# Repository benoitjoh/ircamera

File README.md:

# ircamera

## to install on raspberrypi as user pi

login as user pi

git clone git@github.com:benoitjoh/ircamera.git

cd ircamera

sudo ./install.sh

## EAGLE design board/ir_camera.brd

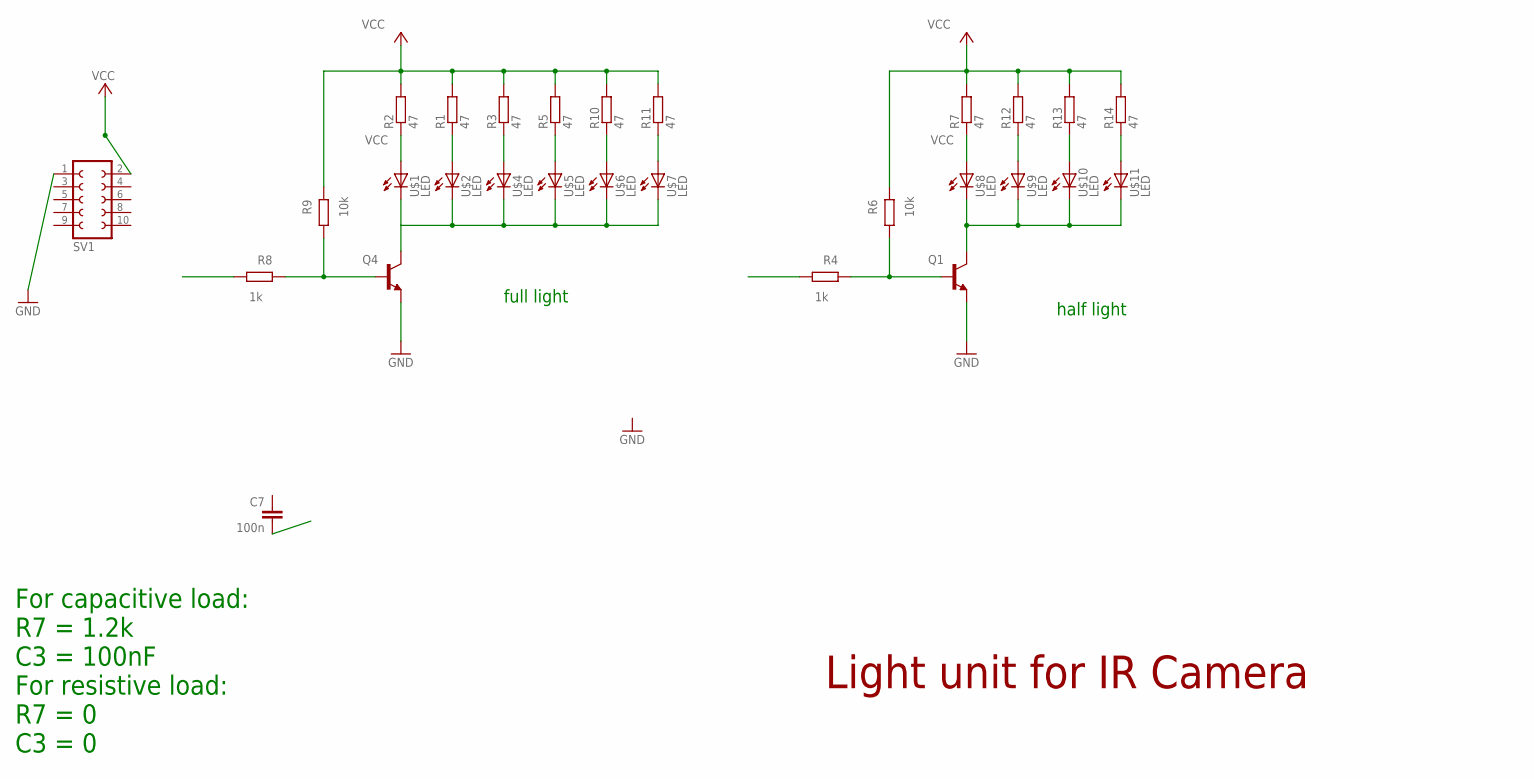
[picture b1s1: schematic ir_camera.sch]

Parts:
C7: 100n; C050-024X044
Q1, Q4: BC548; TO92-EBC
R1, R2, R3, R5, R7, R10, R11, R12, R13, R14: 47; R_0207/2V
R4, R8: 1k; R_0207/2V
R6, R9: 10k; R_0207/2V
SV1: FE05-2
U$1, U$2, U$4, U$5, U$6, U$7, U$8, U$9, U$10, U$11: LED; LED_LD260

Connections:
GND: Q1.E, Q4.E, SV1.1
unnamed: Q4.B, R8.1, R9.1
unnamed: R2.1, U$1.A
unnamed: R1.1, U$2.A
unnamed: R3.1, U$4.A
unnamed: R5.1, U$5.A
unnamed: R10.1, U$6.A
unnamed: R11.1, U$7.A
unnamed: Q4.C, U$1.K (C), U$2.K (C), U$4.K (C), U$5.K (C), U$6.K (C), U$7.K (C)
unnamed: Q1.B, R4.1, R6.1
unnamed: R7.1, U$8.A
unnamed: R12.1, U$9.A
unnamed: R13.1, U$10.A
unnamed: R14.1, U$11.A
unnamed: Q1.C, U$8.K (C), U$9.K (C), U$10.K (C), U$11.K (C)
VCC: R1.2, R2.2, R3.2, R5.2, R6.2, R7.2, R9.2, R10.2, R11.2, R12.2, R13.2, R14.2, SV1.2

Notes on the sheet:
Light unit for IR Camera
half light
full light
For capacitive load: R7 = 1.2k C3 = 100nF For resistive load: R7 = 0 C3 = 0

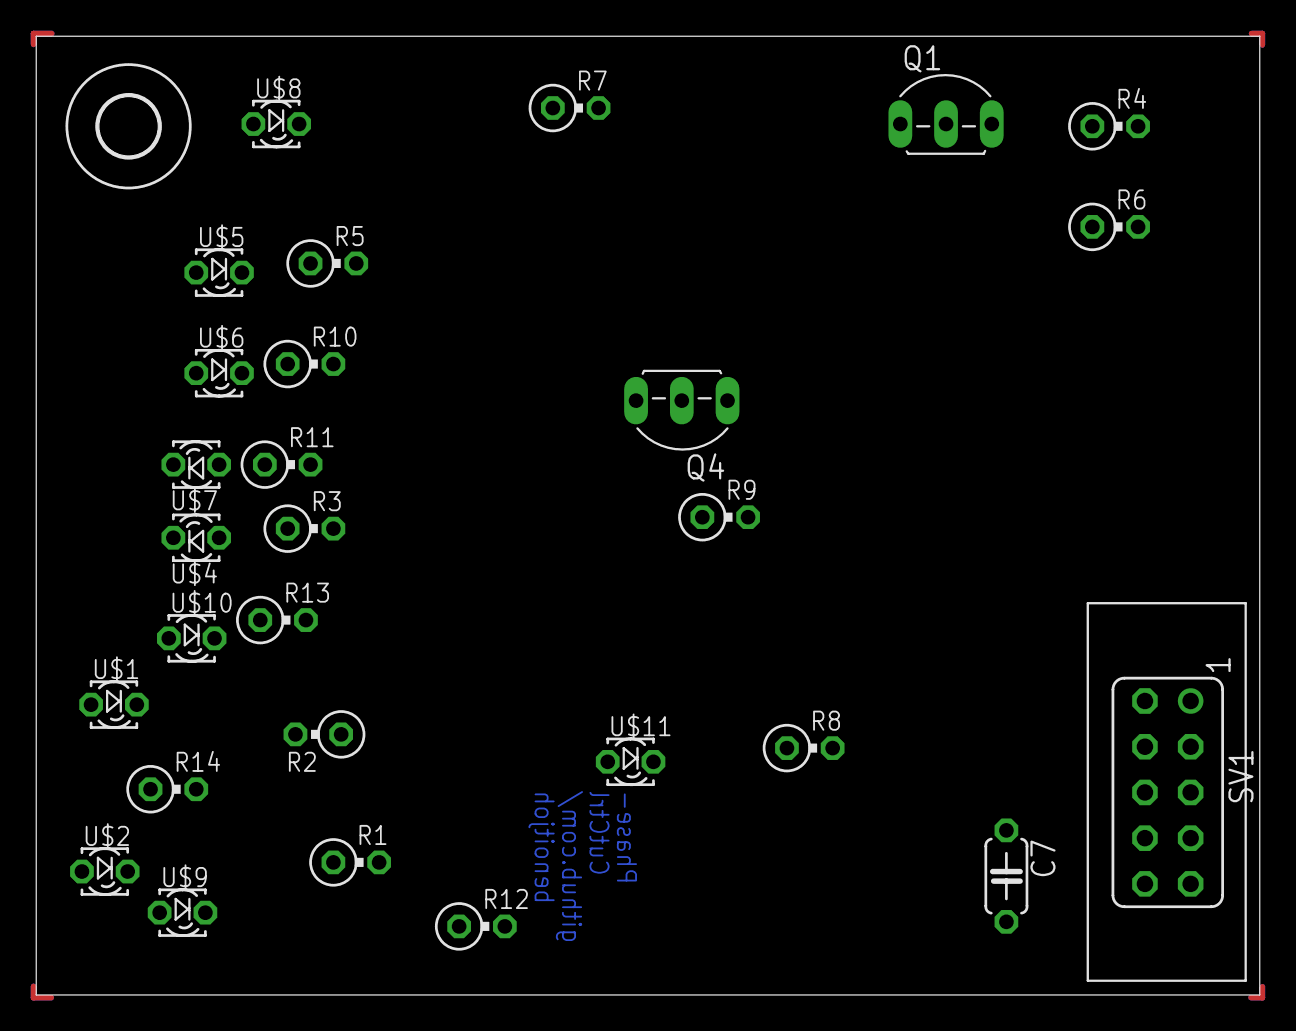
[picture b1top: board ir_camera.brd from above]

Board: 2 copper layers, 68.0 x 53.3 mm, 29 parts (0 on the bottom side), 16 nets.

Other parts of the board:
U$3: 3,3

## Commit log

2020-06-28 initial
2020-06-28 created
2020-06-28 install htop and copy motion.conf
2020-06-28 reduce complexibility
2021-01-14 fix install, add a mask.pmg as example
2021-01-14 increase hysteresis and loopdelay to prevent flickering
2021-01-14 no marker in picture
2021-01-15 use subfolders for pictures
2021-01-17 use timer instead of loop counter to determine recovery of capacitor
2021-01-17 use python3 for time_ns()
2021-02-10 write tempfile with status
2021-02-10 typo
